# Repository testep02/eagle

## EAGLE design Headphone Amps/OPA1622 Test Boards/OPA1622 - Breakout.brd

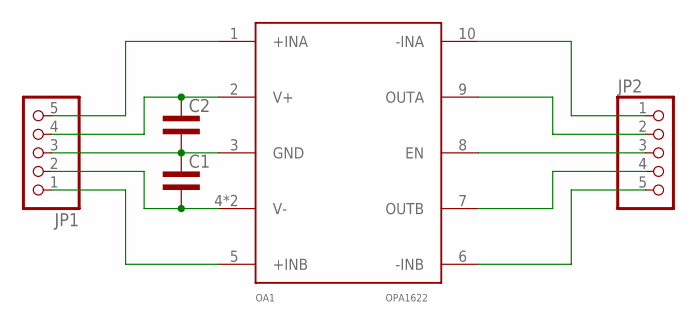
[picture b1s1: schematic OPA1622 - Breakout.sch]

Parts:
C1, C2: CAP0603L3; 0603L3
JP1, JP2: PINHD-1X5; 1X05
OA1: OPA1622; S-PVSON-N10

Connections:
+INA: JP1.5, OA1.1 (+INA)
+INB: JP1.1, OA1.5 (+INB)
-INA: JP2.1, OA1.10 (-INA)
-INB: JP2.5, OA1.6 (-INB)
EN: JP2.3, OA1.8 (EN)
GND: C1.P$1 (1), C2.P$2 (2), JP1.3, OA1.3 (GND)
OUTA: JP2.2, OA1.9 (OUTA)
OUTB: JP2.4, OA1.7 (OUTB)
V+: C2.P$1 (1), JP1.4, OA1.2 (V+)
V-: C1.P$2 (2), JP1.2, OA1.4 (V-), OA1.TP (V-)

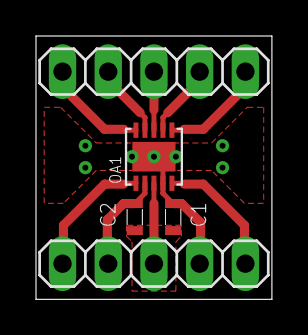
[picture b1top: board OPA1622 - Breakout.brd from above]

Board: 2 copper layers, 13.1 x 14.6 mm, 5 parts (0 on the bottom side), 10 nets.

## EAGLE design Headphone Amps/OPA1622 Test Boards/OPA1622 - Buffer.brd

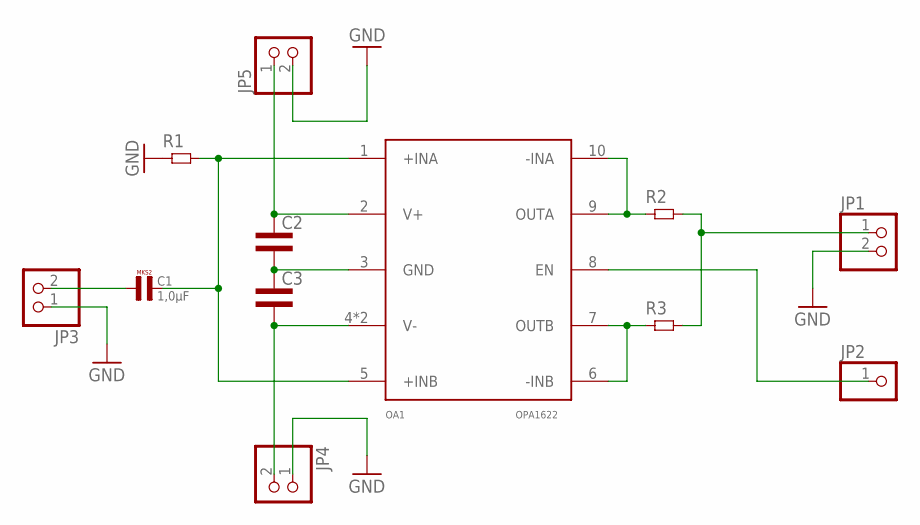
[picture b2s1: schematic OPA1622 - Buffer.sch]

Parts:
C1: 1,0µF; R5B5
C2, C3: CAP0603L3; 0603L3
JP1, JP3, JP4, JP5: PINHD-1X2; 1X02
JP2: PINHD-1X1; 1X01
OA1: OPA1622; S-PVSON-N10
R1: RES0603L3; 0603L3
R2, R3: RES0805L3; 0805L3

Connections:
GND: JP1.2, JP3.1, JP4.1, JP5.2, R1.P$1 (1)
unnamed: OA1.9 (OUTA), OA1.10 (-INA), R2.1
unnamed: OA1.6 (-INB), OA1.7 (OUTB), R3.1
unnamed: JP1.1, R2.2, R3.2
unnamed: C1.1, JP3.2
unnamed: C2.P$2 (2), C3.P$1 (1), OA1.3 (GND)
unnamed: C3.P$2 (2), JP4.2, OA1.4 (V-), OA1.TP (V-)
unnamed: C2.P$1 (1), JP5.1, OA1.2 (V+)
unnamed: JP2.1, OA1.8 (EN)
unnamed: C1.2, OA1.1 (+INA), OA1.5 (+INB), R1.P$2 (2)

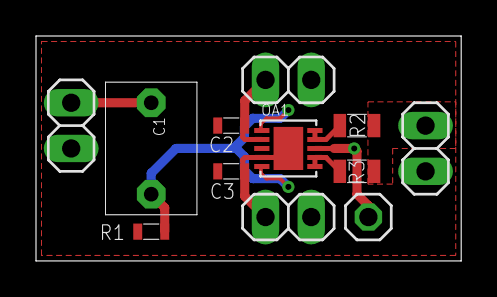
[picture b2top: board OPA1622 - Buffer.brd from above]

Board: 2 copper layers, 23.6 x 12.5 mm, 12 parts (0 on the bottom side), 10 nets.

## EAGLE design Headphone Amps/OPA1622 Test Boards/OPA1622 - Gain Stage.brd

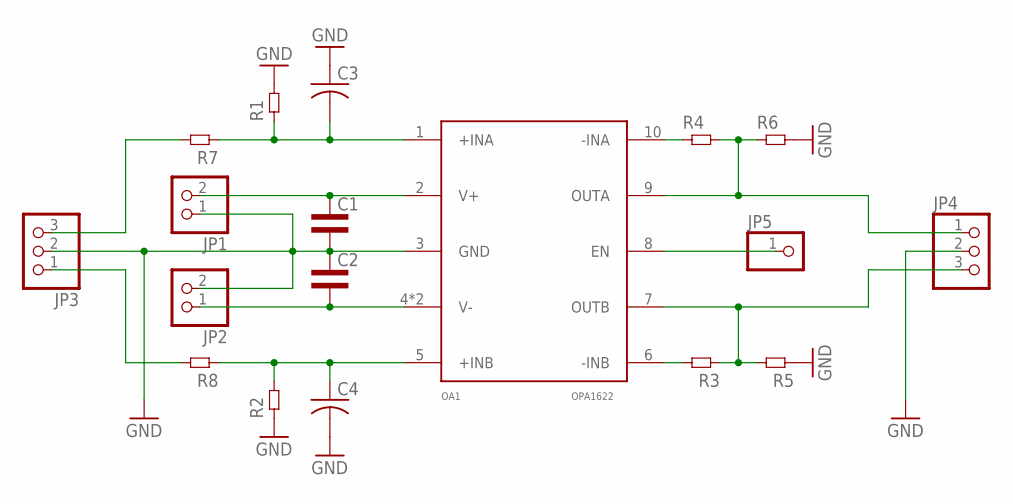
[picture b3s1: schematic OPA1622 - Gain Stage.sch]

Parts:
C1, C2: CAP0603L3; 0603L3
C3, C4: C-US025-050X050; C025-050X050
JP1, JP2: PINHD-1X2; 1X02
JP3, JP4: PINHD-1X3; 1X03
JP5: PINHD-1X1; 1X01
OA1: OPA1622; S-PVSON-N10
R1, R2, R3, R4, R5, R6, R7, R8: RES0603L3; 0603L3

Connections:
GND: C1.P$2 (2), C2.P$1 (1), C3.1, C4.2, JP1.1, JP2.2, JP3.2, JP4.2, OA1.3 (GND), R1.P$2 (2), R2.P$1 (1), R5.P$1 (1), R6.P$2 (2)
unnamed: OA1.6 (-INB), R3.P$2 (2)
unnamed: OA1.10 (-INA), R4.P$1 (1)
unnamed: JP4.1, OA1.9 (OUTA), R4.P$2 (2), R6.P$1 (1)
unnamed: C4.1, OA1.5 (+INB), R2.P$2 (2), R8.P$1 (1)
unnamed: C3.2, OA1.1 (+INA), R1.P$1 (1), R7.P$1 (1)
unnamed: JP4.3, OA1.7 (OUTB), R3.P$1 (1), R5.P$2 (2)
unnamed: JP3.3, R7.P$2 (2)
unnamed: JP3.1, R8.P$2 (2)
unnamed: JP5.1, OA1.8 (EN)
V+: C1.P$1 (1), JP1.2, OA1.2 (V+)
V-: C2.P$2 (2), JP2.1, OA1.4 (V-), OA1.TP (V-)

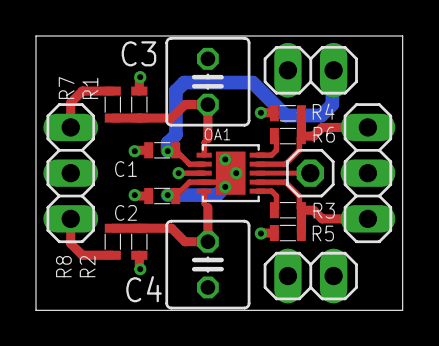
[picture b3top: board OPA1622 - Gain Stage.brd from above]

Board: 2 copper layers, 20.4 x 15.2 mm, 18 parts (0 on the bottom side), 12 nets.

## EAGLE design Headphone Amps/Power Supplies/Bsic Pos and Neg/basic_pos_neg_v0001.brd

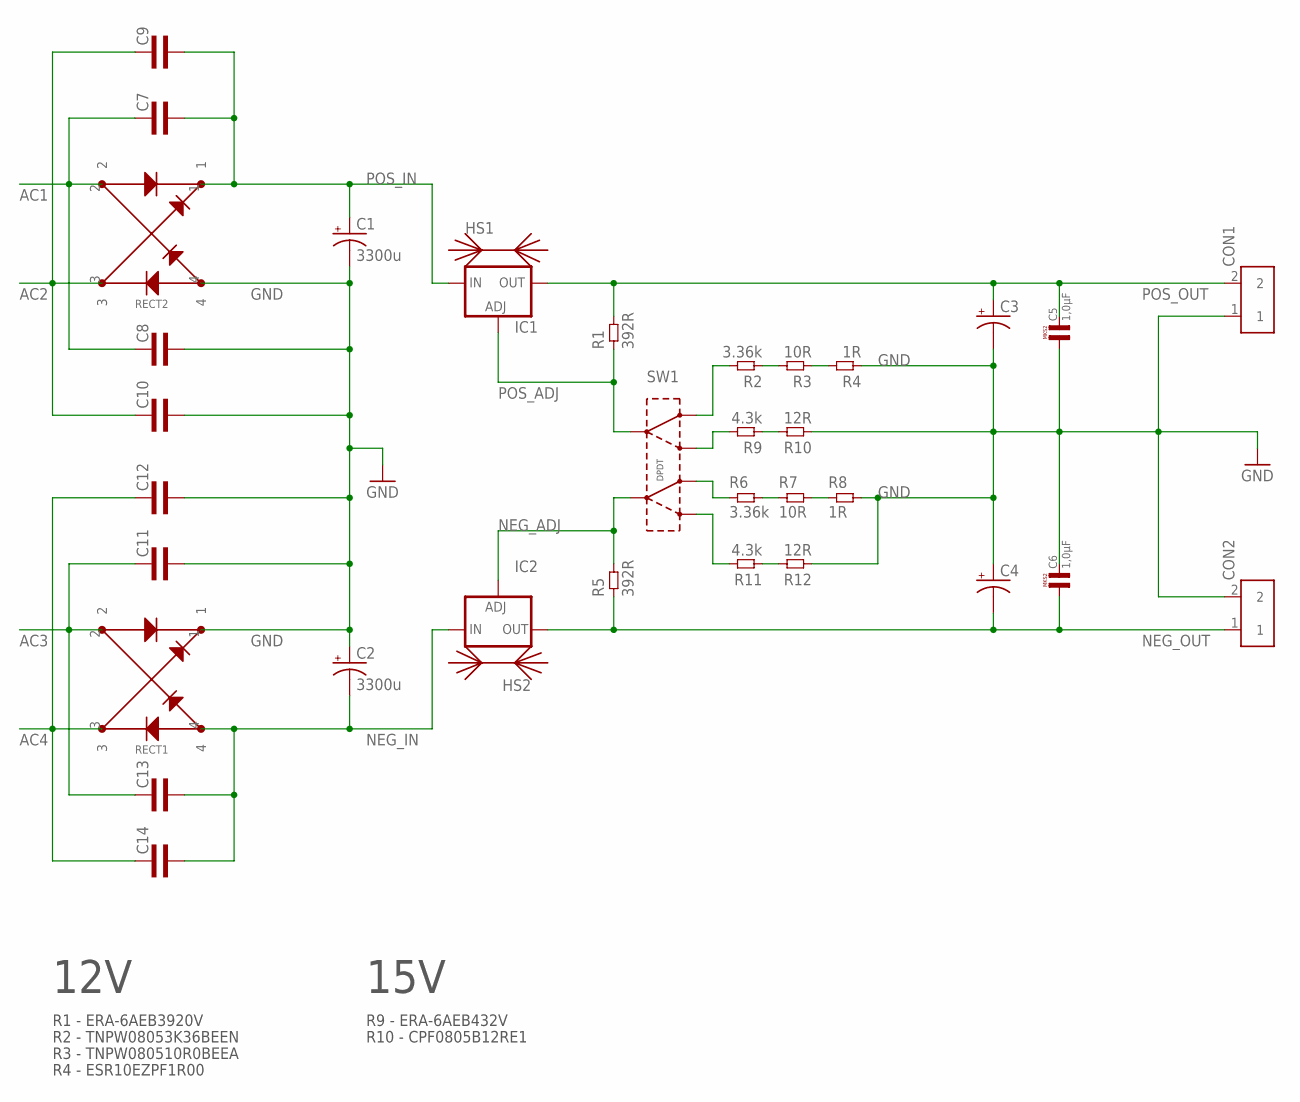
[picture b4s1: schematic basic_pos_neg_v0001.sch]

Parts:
C1, C2: 3300u; E7,5-18
C3, C4: CPOL-USE3.5-8; E3,5-8
C5, C6: 1,0µF; R5B5
C7, C8, C9, C10, C11, C12, C13, C14: CAP0805L3; 0805L3
CON1, CON2: TERM_BLOCK_2
HS1, HS2: HEATSINKTO-220-R; HEATSINK-TO-220-R
IC1: LM317TS; 317TS
IC2: LM337TS; 337TS
R1, R5: 392R; 0805L3
R2, R6: 3.36k; 0805L3
R3, R7: 10R; 0805L3
R4, R8: 1R; 0805L3
R9, R11: 4.3k; 0805L3
R10, R12: 12R; 0805L3
RECT1, RECT2: RECTIFIER_Z4GP206; RECTIFIER_ABS-4
SW1: DPDT; WIRES-2X6-14G

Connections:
AC1: C7.1, C8.1, RECT2.2
AC2: C9.1, C10.1, RECT2.3
AC3: C11.1, C13.1, RECT1.2
AC4: C12.1, C14.1, RECT1.3
GND: C1.-, C2.+, C3.-, C4.+, C5.1, C6.2, C8.2, C10.2, C11.2, C12.2, CON1.1, CON2.2, R4.1, R8.2, R10.1, R12.1, RECT1.1, RECT2.4
unnamed: R9.2, SW1.3 (OUTA2)
unnamed: R6.2, R7.1
unnamed: R2.2, SW1.1 (OUTA1)
unnamed: R7.2, R8.1
unnamed: R6.1, SW1.6 (OUTB1)
unnamed: R2.1, R3.2
unnamed: R11.2, SW1.4 (OUTB2)
unnamed: R3.1, R4.2
unnamed: R9.1, R10.2
unnamed: R11.1, R12.2
NEG_ADJ: IC2.1 (ADJ), R5.2, SW1.5 (INB)
NEG_IN: C2.-, C13.2, C14.2, IC2.2 (IN), RECT1.4
NEG_OUT: C4.-, C6.1, CON2.1, IC2.3 (OUT), R5.1
POS_ADJ: IC1.1 (ADJ), R1.1, SW1.2 (INA)
POS_IN: C1.+, C7.2, C9.2, IC1.3 (IN), RECT2.1
POS_OUT: C3.+, C5.2, CON1.2, IC1.2 (OUT), R1.2

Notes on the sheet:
R2 - TNPW08053K36BEEN
R1 - ERA-6AEB3920V
R3 - TNPW080510R0BEEA
R4 - ESR10EZPF1R00
12V
15V
R9 - ERA-6AEB432V
R10 - CPF0805B12RE1

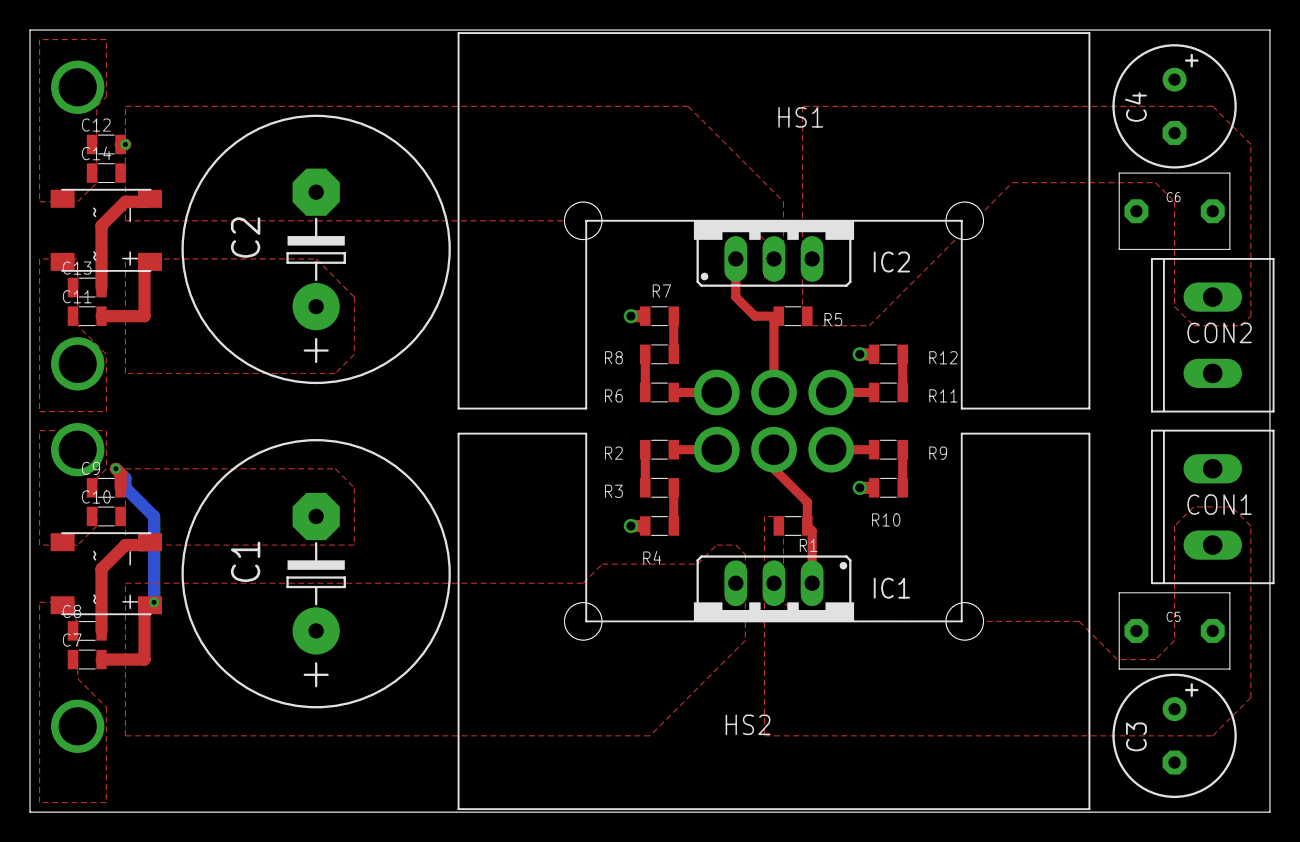
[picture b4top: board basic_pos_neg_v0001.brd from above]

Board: 2 copper layers, 82.5 x 52.1 mm, 35 parts (0 on the bottom side), 21 nets.

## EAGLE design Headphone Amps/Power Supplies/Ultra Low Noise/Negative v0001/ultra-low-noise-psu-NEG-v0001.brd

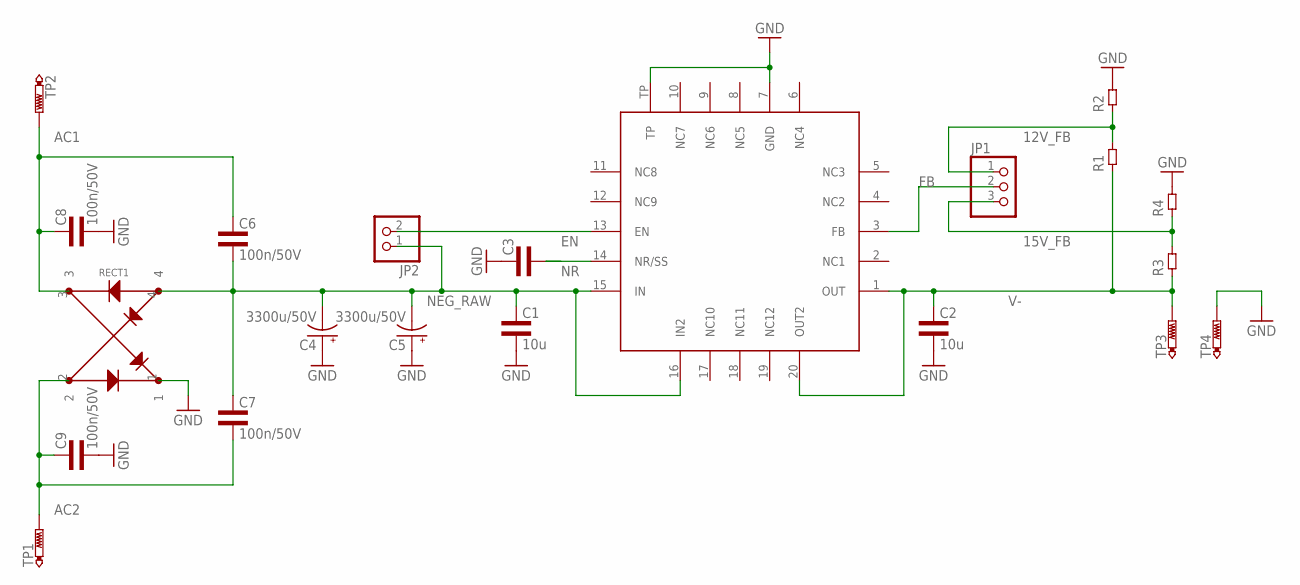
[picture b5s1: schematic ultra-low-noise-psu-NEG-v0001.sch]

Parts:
C1, C2: 10u; 0805L3
C3: CAP0603L3; 0603L3
C4, C5: 3300u/50V; E7,5-18
C6, C7, C8, C9: 100n/50V; 0805L3
JP1: PINHD-1X3; 1X03
JP2: PINHD-1X2; 1X02
R1, R2, R3, R4: RES0603L3; 0603L3
RECT1: RECTIFIER_Z4GP206; RECTIFIER_ABS-4
TP1, TP2, TP3, TP4: PTR1PAD1-20; P1-20
U$1: POWER-SUPPLY_POS_V1_TI_LDO_TPS7A3301RGWT; POWER-SUPPLY_POS_V1_TI_LDO_VQFN-20

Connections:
12V_FB: JP1.1, R1.P$2 (2), R2.P$1 (1)
15V_FB: JP1.3, R3.P$2 (2), R4.P$1 (1)
AC1: C6.1, C8.1, RECT1.3, TP2.TP
AC2: C7.2, C9.1, RECT1.2, TP1.TP
EN: JP2.2, U$1.13 (EN)
FB: JP1.2, U$1.3 (FB)
GND: C1.2, C2.2, C3.P$1 (1), C4.+, C5.+, C8.2, C9.2, R2.P$2 (2), R4.P$2 (2), RECT1.1, TP4.TP, U$1.7 (GND), U$1.TP
NEG_RAW: C1.1, C4.-, C5.-, C6.2, C7.1, JP2.1, RECT1.4, U$1.15 (IN), U$1.16 (IN2)
NR: C3.P$2 (2), U$1.14 (NR/SS)
V-: C2.1, R1.P$1 (1), R3.P$1 (1), TP3.TP, U$1.1 (OUT), U$1.20 (OUT2)

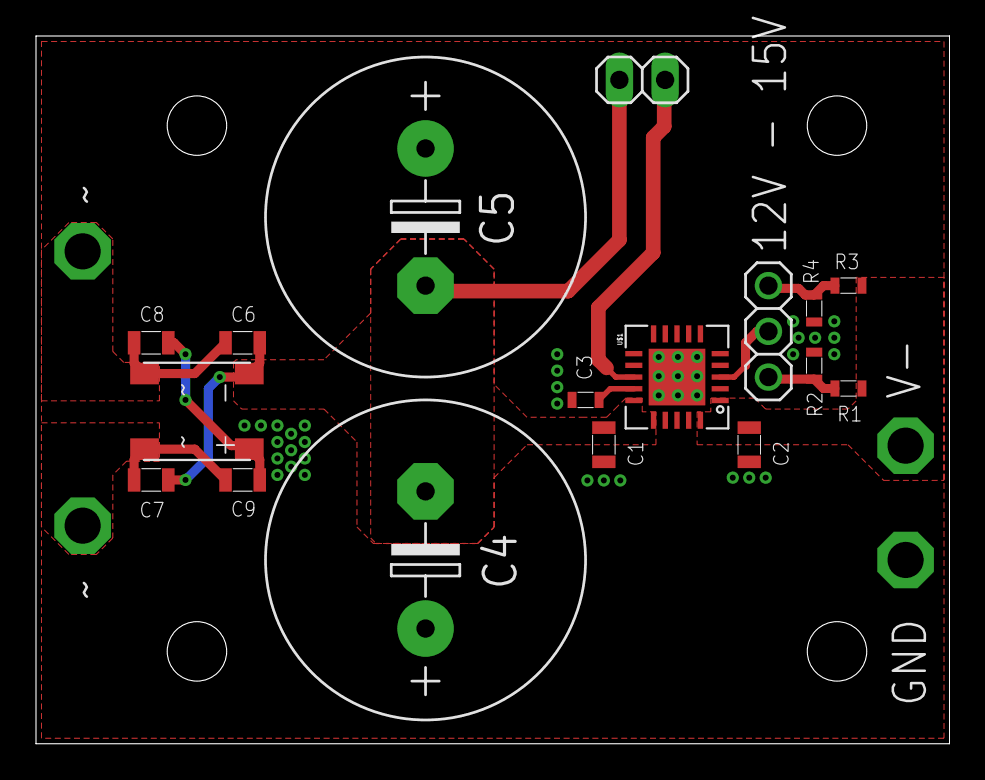
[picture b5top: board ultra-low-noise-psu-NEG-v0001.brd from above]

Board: 2 copper layers, 50.7 x 39.3 mm, 21 parts (0 on the bottom side), 10 nets.

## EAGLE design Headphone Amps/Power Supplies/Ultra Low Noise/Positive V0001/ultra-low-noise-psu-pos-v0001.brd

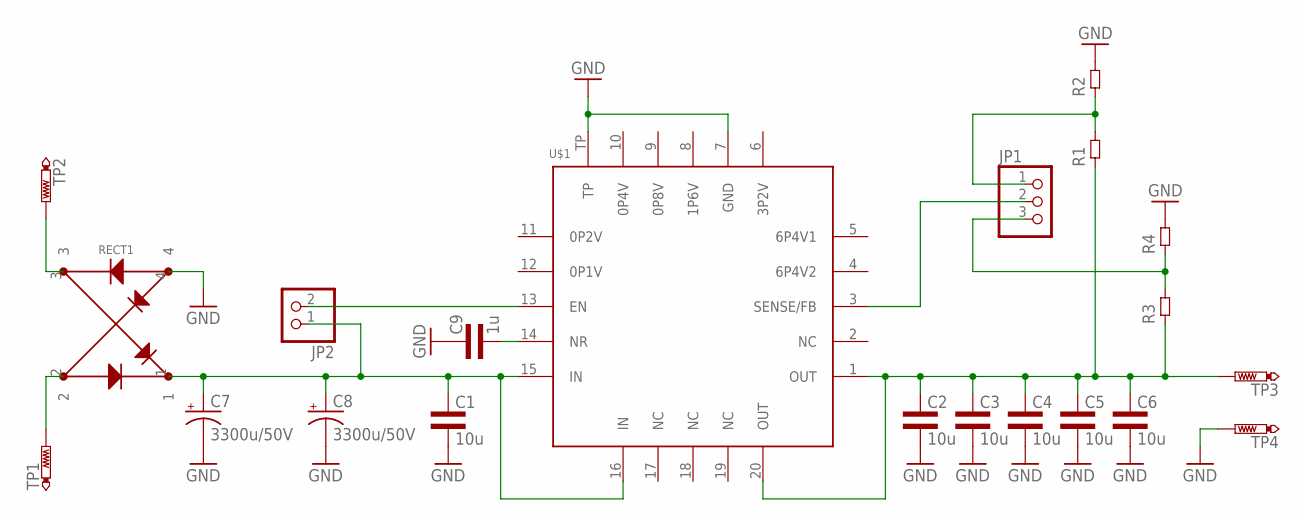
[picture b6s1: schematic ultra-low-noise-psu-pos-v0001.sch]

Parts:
C1, C2, C3, C4, C5, C6: 10u; 0805L3
C7, C8: 3300u/50V; E7,5-18
C9: 1u; 0603L3
JP1: PINHD-1X3; 1X03
JP2: PINHD-1X2; 1X02
R1, R2, R3, R4: RES0603L3; 0603L3
RECT1: RECTIFIER_Z4GP206; RECTIFIER_ABS-4
TP1, TP2, TP3, TP4: PTR1PAD1-20; P1-20
U$1: POWER-SUPPLY_POS_V1_TI_LDO_TPS7A4700; POWER-SUPPLY_POS_V1_TI_LDO_VQFN-20

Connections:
GND: C1.2, C2.2, C3.2, C4.2, C5.2, C6.2, C7.-, C8.-, C9.P$1 (1), R2.P$2 (2), R4.P$2 (2), RECT1.4, TP4.TP, U$1.7 (GND), U$1.TP
unnamed: C1.1, C7.+, C8.+, JP2.1, RECT1.1, U$1.15 (IN), U$1.16 (IN)
unnamed: C2.1, C3.1, C4.1, C5.1, C6.1, R1.P$1 (1), R3.P$1 (1), TP3.TP, U$1.1 (OUT), U$1.20 (OUT)
unnamed: JP2.2, U$1.13 (EN)
unnamed: C9.P$2 (2), U$1.14 (NR)
unnamed: JP1.2, U$1.3 (SENSE/FB)
unnamed: JP1.3, R3.P$2 (2), R4.P$1 (1)
unnamed: JP1.1, R1.P$2 (2), R2.P$1 (1)
unnamed: RECT1.2, TP1.TP
unnamed: RECT1.3, TP2.TP

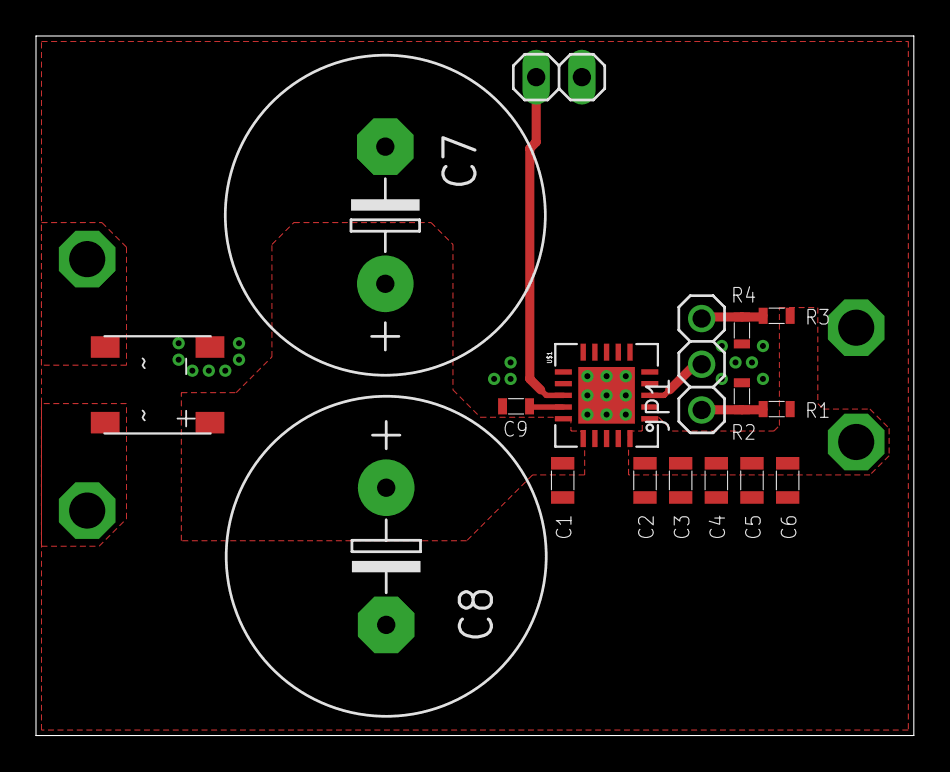
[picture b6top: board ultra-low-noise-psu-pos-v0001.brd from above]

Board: 2 copper layers, 48.8 x 38.9 mm, 21 parts (0 on the bottom side), 10 nets.

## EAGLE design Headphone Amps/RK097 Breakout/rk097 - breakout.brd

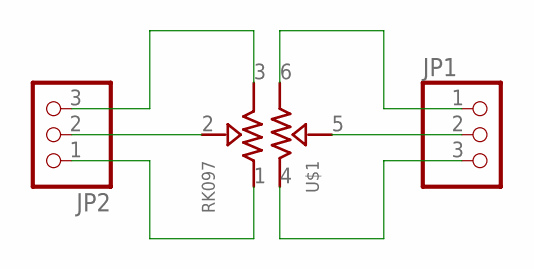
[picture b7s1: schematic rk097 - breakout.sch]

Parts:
JP1, JP2: PINHD-1X3; 1X03
U$1: RK097

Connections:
unnamed: JP2.1, U$1.1
unnamed: JP2.2, U$1.2
unnamed: JP2.3, U$1.3
unnamed: JP1.2, U$1.5
unnamed: JP1.3, U$1.4
unnamed: JP1.1, U$1.6

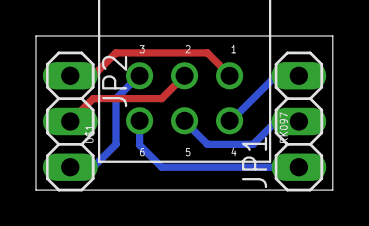
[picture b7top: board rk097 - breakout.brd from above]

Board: 2 copper layers, 16.5 x 8.6 mm, 3 parts (0 on the bottom side), 6 nets.

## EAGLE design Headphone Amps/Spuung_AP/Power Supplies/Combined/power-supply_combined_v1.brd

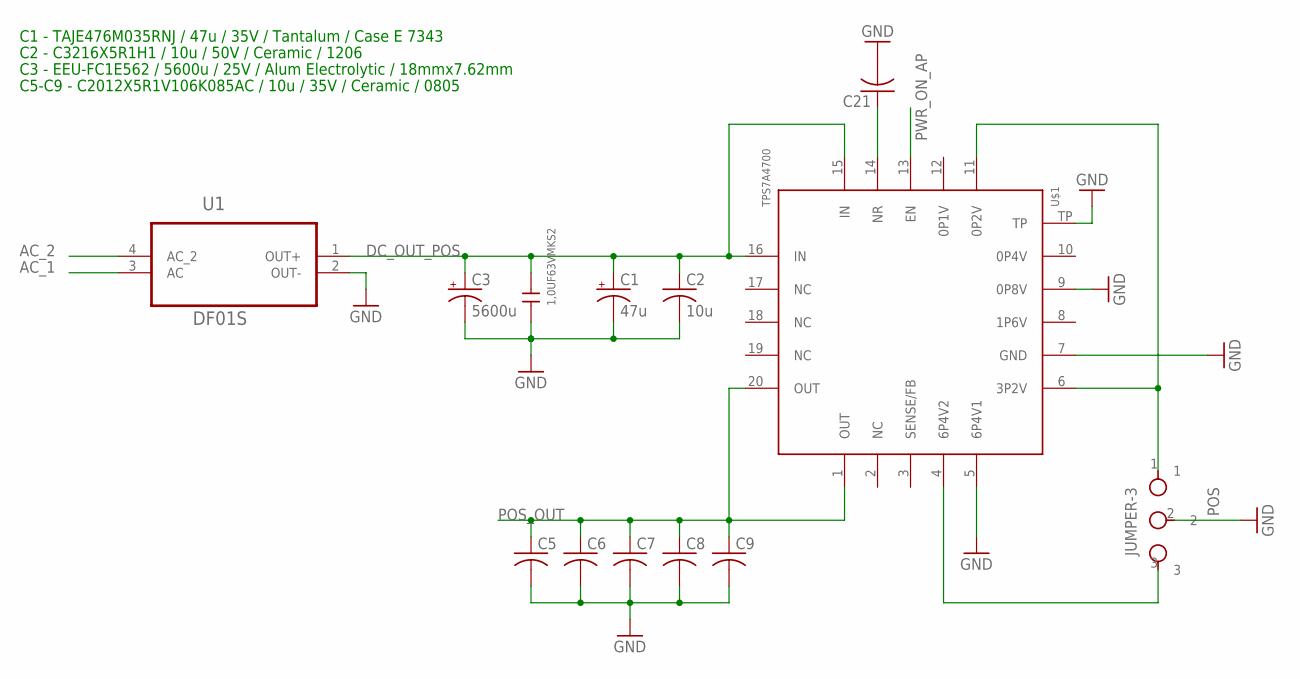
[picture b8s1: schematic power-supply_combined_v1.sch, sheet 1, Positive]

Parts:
C1: 47u; SMC_E
C2: 10u; C1206
C3: 5600u; E7,5-18
C4: 1,0UF63VMKS2; 5,0X10,0RM5,0
C5, C6, C7, C8, C9: C-USC0805; C0805
C21: C-USC0603; C0603
POS: JUMPER-3; 1X03
U1: DF01S; SOT508P985X260-4N
U$1: TPS7A4700; VQFN-20

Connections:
AC_1: U1.3 (AC)
AC_2: U1.4 (AC_2)
DC_OUT_POS: C1.+, C2.1, C3.+, C4.2, U1.1 (OUT+), U$1.15 (IN), U$1.16 (IN); also elsewhere on the board
GND: C1.-, C2.2, C3.-, C4.1, C5.2, C6.2, C7.2, C8.2, C9.2, C21.2, POS.2, U1.2 (OUT-), U$1.5 (6P4V1), U$1.7 (GND), U$1.9 (0P8V), U$1.TP; also elsewhere on the board
unnamed: POS.3, U$1.4 (6P4V2)
unnamed: POS.1, U$1.6 (3P2V), U$1.11 (0P2V)
unnamed: C21.1, U$1.14 (NR)
POS_OUT: C5.1, C6.1, C7.1, C8.1, C9.1, U$1.1 (OUT), U$1.20 (OUT)
PWR_ON_AP: U$1.13 (EN); also elsewhere on the board

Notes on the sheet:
C1 - TAJE476M035RNJ / 47u / 35V / Tantalum / Case E 7343
C2 - C3216X5R1H1 / 10u / 50V / Ceramic / 1206
C3 - EEU-FC1E562 / 5600u / 25V / Alum Electrolytic / 18mmx7.62mm
C5-C9 - C2012X5R1V106K085AC / 10u / 35V / Ceramic / 0805

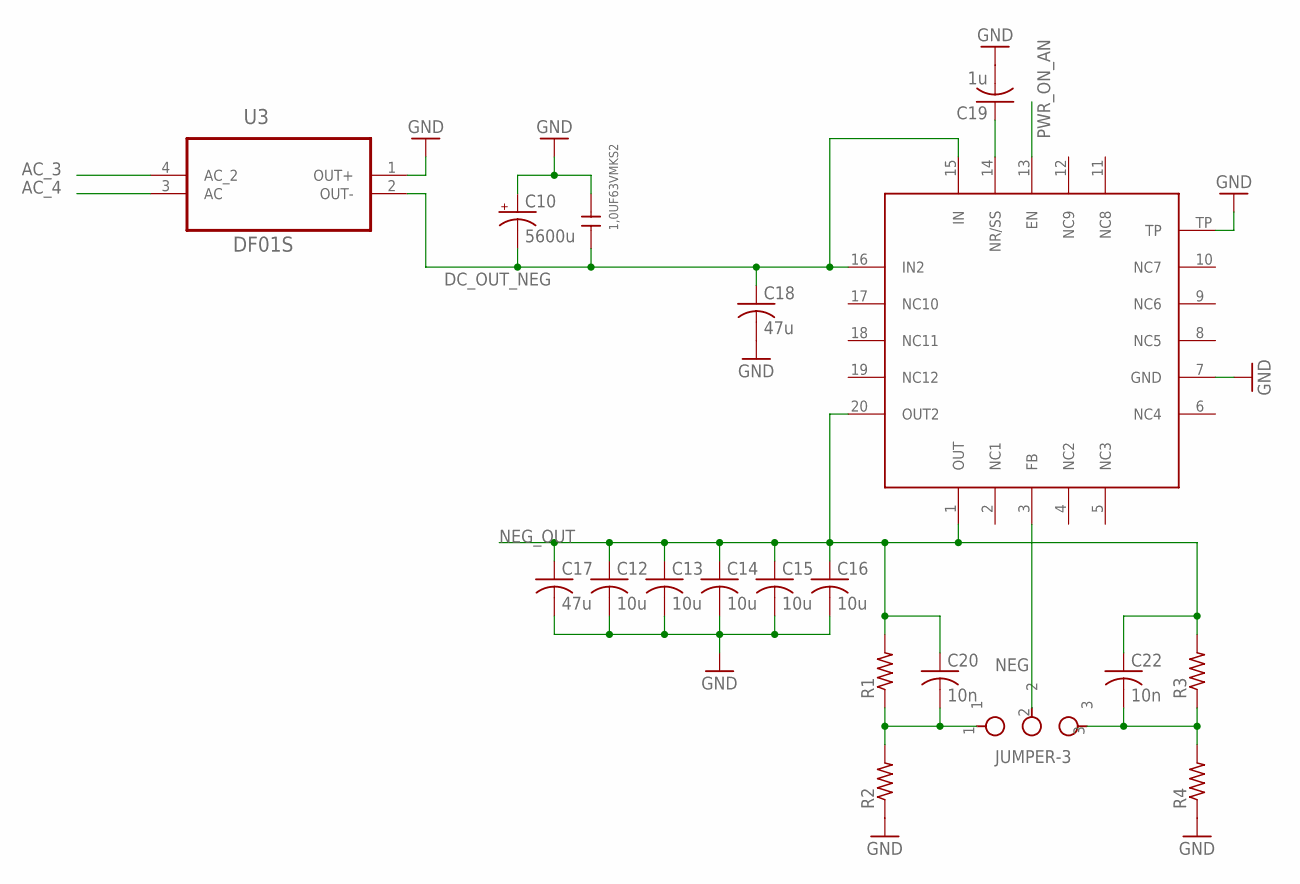
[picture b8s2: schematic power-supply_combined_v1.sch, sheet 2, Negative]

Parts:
C10: 5600u; E7,5-18
C11: 1,0UF63VMKS2; 5,0X10,0RM5,0
C12, C13, C14, C15, C16: 10u; C0805
C17, C18: 47u; C2220K
C19: 1u; C0603
C20, C22: 10n; C0603
NEG: JUMPER-3; 1X03
R1, R2, R3, R4: R-US_R0603; R0603
U3: DF01S; SOT508P985X260-4N
U$2: TPS7A3301RGWT; VQFN-20

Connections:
AC_3: U3.4 (AC_2)
AC_4: U3.3 (AC)
DC_OUT_NEG: C10.-, C11.1, C18.1, U3.2 (OUT-), U$2.15 (IN), U$2.16 (IN2); also elsewhere on the board
GND: C10.+, C11.2, C12.2, C13.2, C14.2, C15.2, C16.2, C17.2, C18.2, C19.2, R2.1, R4.1, U3.1 (OUT+), U$2.7 (GND), U$2.TP; also elsewhere on the board
unnamed: C20.2, NEG.1, R1.1, R2.2
unnamed: C19.1, U$2.14 (NR/SS)
unnamed: C22.2, NEG.3, R3.1, R4.2
unnamed: NEG.2, U$2.3 (FB)
NEG_OUT: C12.1, C13.1, C14.1, C15.1, C16.1, C17.1, C20.1, C22.1, R1.2, R3.2, U$2.1 (OUT), U$2.20 (OUT2)
PWR_ON_AN: U$2.13 (EN); also elsewhere on the board

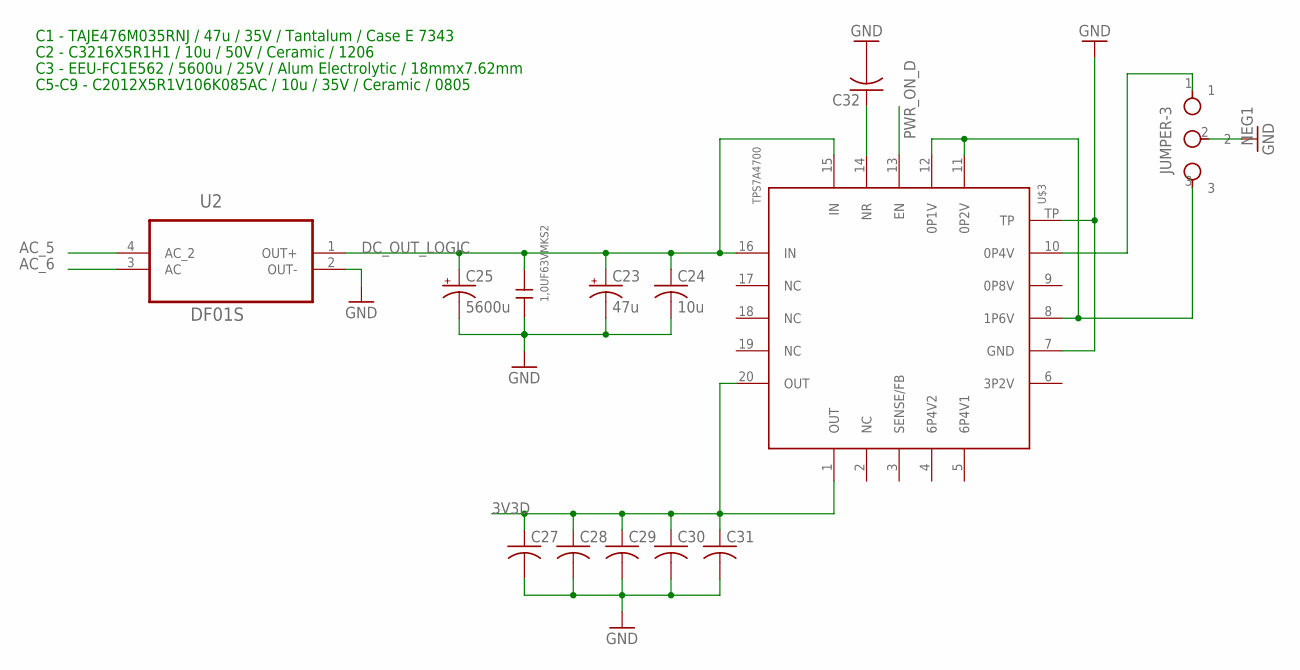
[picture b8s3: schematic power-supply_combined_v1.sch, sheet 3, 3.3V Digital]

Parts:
C23: 47u; SMC_E
C24: 10u; C1206
C25: 5600u; E7,5-18
C26: 1,0UF63VMKS2; 5,0X10,0RM5,0
C27, C28, C29, C30, C31: C-USC0805; C0805
C32: C-USC0603; C0603
NEG1: JUMPER-3; 1X03
U2: DF01S; SOT508P985X260-4N
U$3: TPS7A4700; VQFN-20

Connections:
3V3D: C27.1, C28.1, C29.1, C30.1, C31.1, U$3.1 (OUT), U$3.20 (OUT)
AC_5: U2.4 (AC_2)
AC_6: U2.3 (AC)
DC_OUT_LOGIC: C23.+, C24.1, C25.+, C26.2, U2.1 (OUT+), U$3.15 (IN), U$3.16 (IN); also elsewhere on the board
GND: C23.-, C24.2, C25.-, C26.1, C27.2, C28.2, C29.2, C30.2, C31.2, C32.2, NEG1.2, U2.2 (OUT-), U$3.7 (GND), U$3.TP; also elsewhere on the board
unnamed: C32.1, U$3.14 (NR)
unnamed: NEG1.3, U$3.8 (1P6V), U$3.11 (0P2V), U$3.12 (0P1V)
unnamed: NEG1.1, U$3.10 (0P4V)
PWR_ON_D: U$3.13 (EN); also elsewhere on the board

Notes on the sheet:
C1 - TAJE476M035RNJ / 47u / 35V / Tantalum / Case E 7343
C2 - C3216X5R1H1 / 10u / 50V / Ceramic / 1206
C3 - EEU-FC1E562 / 5600u / 25V / Alum Electrolytic / 18mmx7.62mm
C5-C9 - C2012X5R1V106K085AC / 10u / 35V / Ceramic / 0805

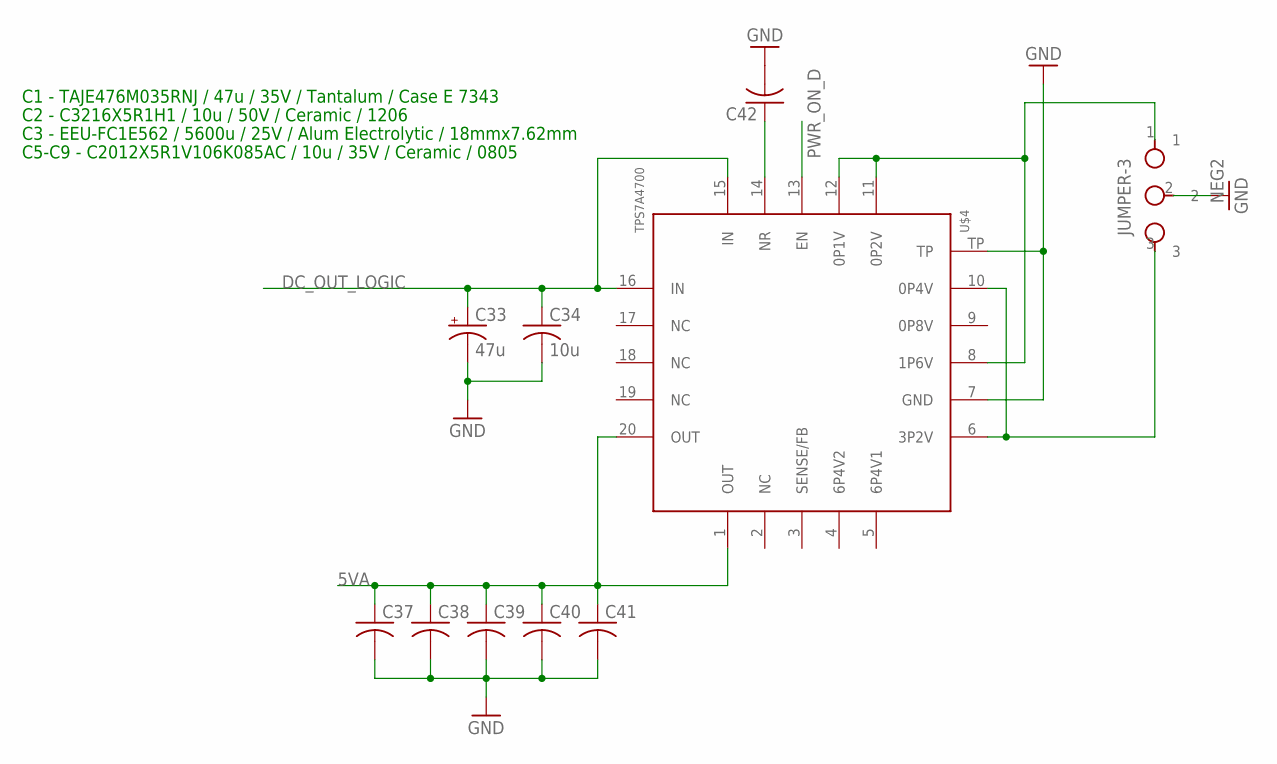
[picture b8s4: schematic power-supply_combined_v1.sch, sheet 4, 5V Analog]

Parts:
C33: 47u; SMC_E
C34: 10u; C1206
C37, C38, C39, C40, C41: C-USC0805; C0805
C42: C-USC0603; C0603
NEG2: JUMPER-3; 1X03
U$4: TPS7A4700; VQFN-20

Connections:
5VA: C37.1, C38.1, C39.1, C40.1, C41.1, U$4.1 (OUT), U$4.20 (OUT)
DC_OUT_LOGIC: C33.+, C34.1, U$4.15 (IN), U$4.16 (IN); also elsewhere on the board
GND: C33.-, C34.2, C37.2, C38.2, C39.2, C40.2, C41.2, C42.2, NEG2.2, U$4.7 (GND), U$4.TP; also elsewhere on the board
unnamed: NEG2.3, U$4.6 (3P2V), U$4.10 (0P4V)
unnamed: NEG2.1, U$4.8 (1P6V), U$4.11 (0P2V), U$4.12 (0P1V)
unnamed: C42.1, U$4.14 (NR)
PWR_ON_D: U$4.13 (EN); also elsewhere on the board

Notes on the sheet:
C1 - TAJE476M035RNJ / 47u / 35V / Tantalum / Case E 7343
C2 - C3216X5R1H1 / 10u / 50V / Ceramic / 1206
C3 - EEU-FC1E562 / 5600u / 25V / Alum Electrolytic / 18mmx7.62mm
C5-C9 - C2012X5R1V106K085AC / 10u / 35V / Ceramic / 0805

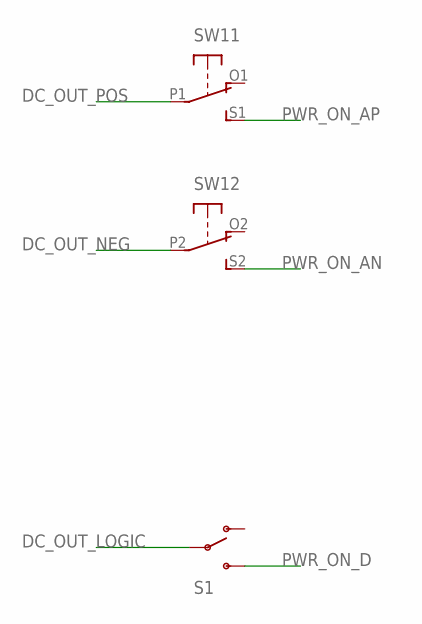
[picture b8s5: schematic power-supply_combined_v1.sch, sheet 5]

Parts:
S1: SWITCH-SPDTSMD; AYZ0202
SW1: DPDT-EG1390; EG1390

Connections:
DC_OUT_LOGIC: S1.2; also elsewhere on the board
DC_OUT_NEG: SW1.P2; also elsewhere on the board
DC_OUT_POS: SW1.P1; also elsewhere on the board
PWR_ON_AN: SW1.S2 (S); also elsewhere on the board
PWR_ON_AP: SW1.S1 (S); also elsewhere on the board
PWR_ON_D: S1.3 (S); also elsewhere on the board

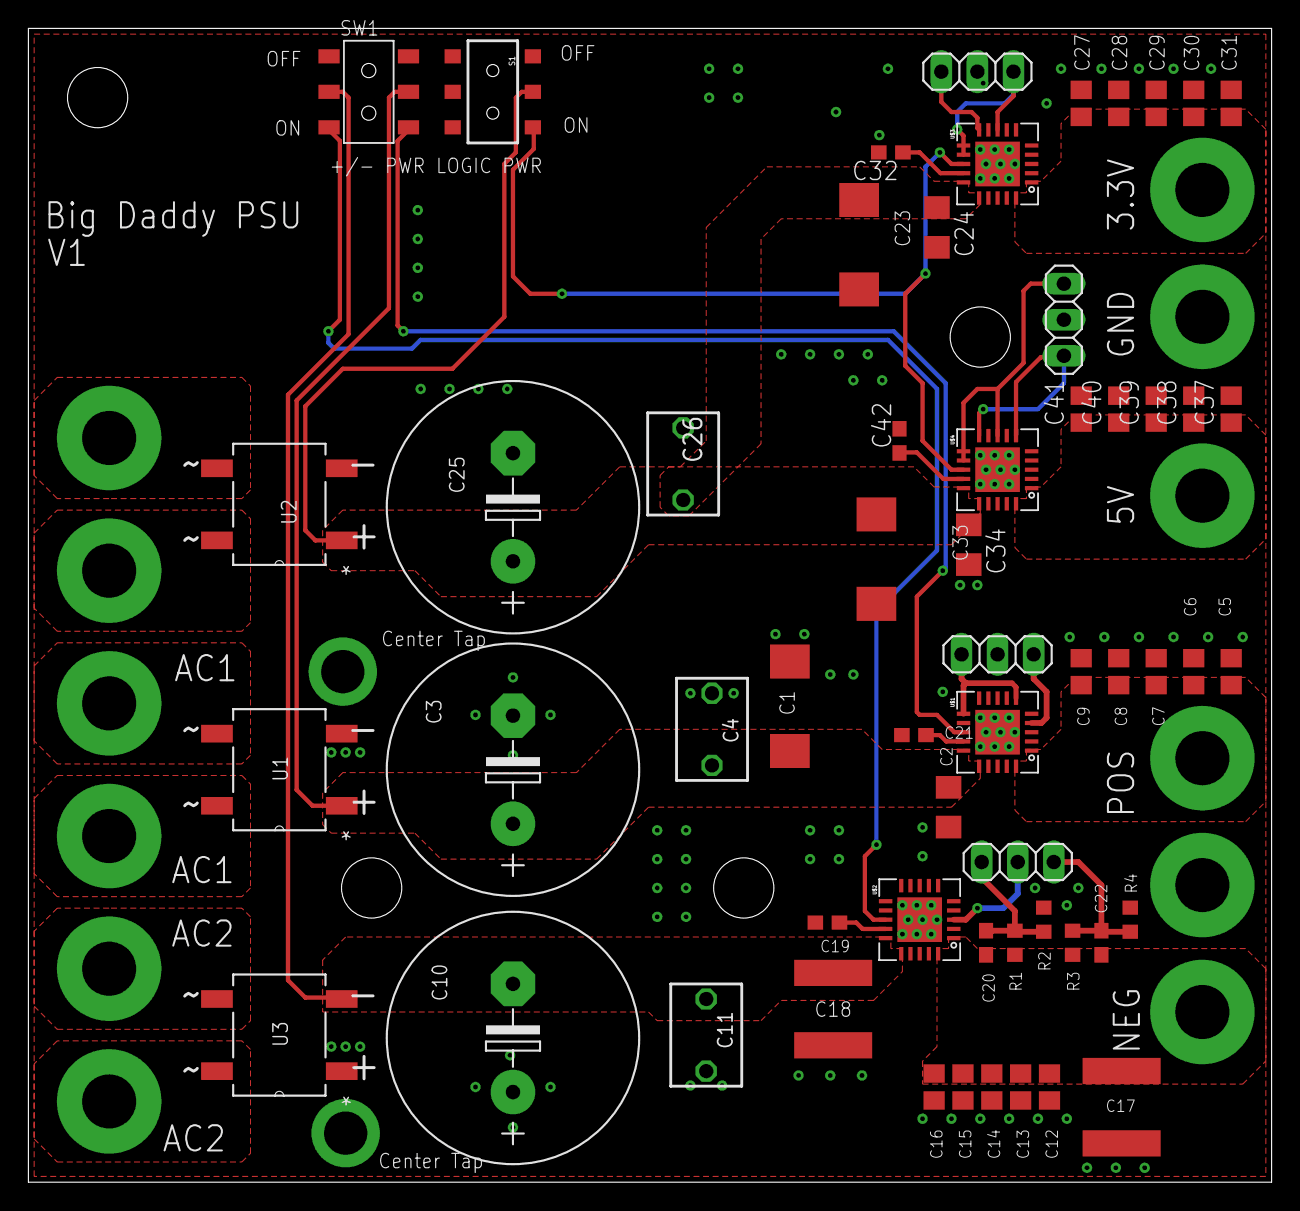
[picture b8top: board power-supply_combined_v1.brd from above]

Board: 2 copper layers, 87.6 x 81.3 mm, 57 parts (0 on the bottom side), 24 nets.

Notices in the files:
parts and their libraries:
SparkFun-Aesthetics: Licensing: CC v3.0 Share-Alike You are welcome to use this library for commercial purposes.
